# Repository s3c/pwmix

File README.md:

The pwmix project is a small hardware device that can alter PWM/PPM signals generated by common hobby remote controls. This allows enabling mixing for cheap RC transmitters, or where the receiver applies some mechanism that isn't desired. It is based on the Attiny85 but smaller micro controllers like the Attiny25 can  be used, you'll need a pretty steady hand to make it fit on the edge of the larger footprint though. 

The unit supports two inputs and two outputs, although these are identical and can potentially be used otherwise. With the micro controller facing upwards, the top left channel is input channel one, the bottom left channel is input two, the bottom right channel is output one, and the top right channel is output two. By convention, input one is considered the main input, and input two is considered the modulating input.

Since the Attiny85 has an inaccurate internal timer, rather than adding a crystal the unit does a clock sync to sync with the receiver. This is done by adjusting the internal clock using a binary search at startup, to match the expected pulse length with what is received. This is done on input channel one, and the expected value differs between code features.

The project was created with the following in mind:

* (DONE) Differential drive mixing - the main input takes a motor drive, while the second takes a servo turning signal. These are mixed together to output two motor drive signals mixed to provide differential drive. This allows the use of two motors to drive and steer, as opposed to a motor and a servo. Initial sync should be at mid stick (1.5mS PWM pulse)
* Servo limiting (planned) - the main input takes a servo input, while the optional second input takes a calibration servo signal. If the second signal is present, the minimum and maximum values are stored and saved in EEPROM. The output signals are mirrored and will never exeed the stored limits. To set the limits plug in both signals and vary the second signal between min/max. The input signal is scaled so full input deflection gives full limited output deflection. Initial sync should be at low stick (1mS PWM pulse)
* Fake Nitrous oxide (planned) - the main input takes a motor drive, while the second takes a enable signal. If the enable signal is greater than 3/4 full deflection, the mirrored outputs (following the motor drive signal) are allowed to swing to greater than 50%, if not, the output signals are limited to 50%. When this enable trigger is active, a timer decrements a 30 second limit, which limits the motor to 50% when depleted. This creates a fake boost mechanism, which gives a more dynamic nature to racing. Initial sync should be at mid stick (1.5mS PWM pulse)
* (DONE) PPM to PWM converter - Each board strips off the first two PPM channels and outputs them as PWM, then passes the remaining PPM signal along. This allows daisy chaining the PPM signal along the body of the plane so you only need to run one wire from the receiver and still be able to control all servos/motors, etc.

Known issues (Differential drive mixing):
* There seems to be a dead band/jitter of around 50uS for small values on input two in one direction, this also seems to reflect more on output one than output two for some reason. I don't really know why this is happening, I've confirmed that there is a tiny dead band/jitter on the input channel, but insignificant compared to the output. The inputs/outputs aren't handled differently in any way so some weird race condition is in play here. The most likely scenario is that the edge trigger interrupt fires just before the compare match timer, so the timer interrupt only fires after the edge has been processed, creating a dead band region. The ideal fix for this would be to use the compare match module to automatically turn off the output pins, but the hardware doesn't allow this, as the output pins aren't assigned to the compare match pins. I'll fix this if there's ever another revision. **Update: Ok, I managed to confirm that this was the problem, and I fixed the issue by making the pin change ISR non-blocking and adding a flag to avoid re-entry if another pin change occured. We still have some jitter but that's to be expected considering all the overhead and no crystal. The above fix would still be better though**

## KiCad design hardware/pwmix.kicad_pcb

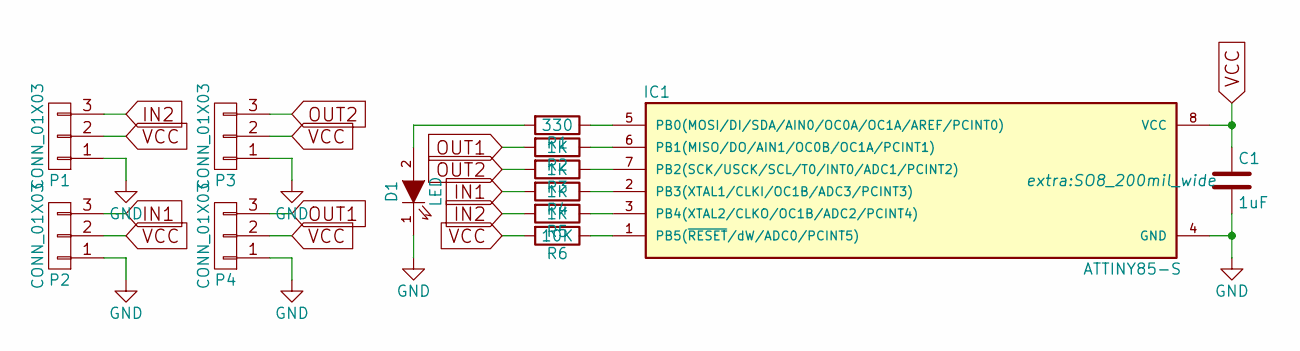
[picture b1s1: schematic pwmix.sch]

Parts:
C1: 1uF; C_0805
D1: LED; LED_0805
IC1: ATTINY85-S; SO8_200mil_wide
P1, P2, P3, P4: CONN_01X03; Pin_Header_Angled_1x03
R1: 330; R_0805
R2, R3, R4, R5: 1K; R_0805
R6: 10K; R_0805

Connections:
GND: C1.2, D1.1 (K), IC1.4 (GND), P1.1, P2.1, P3.1, P4.1
IN1: P2.3, R4.2
IN2: P1.3, R5.2
unnamed: D1.2 (A), R1.2
unnamed: IC1.1 (PB5(~RESET~/dW/ADC0/PCINT5)), R6.1
unnamed: IC1.2 (PB3(XTAL1/CLKI/OC1B/ADC3/PCINT3)), R4.1
unnamed: IC1.3 (PB4(XTAL2/CLKO/OC1B/ADC2/PCINT4)), R5.1
unnamed: IC1.5 (PB0(MOSI/DI/SDA/AIN0/OC0A/OC1A/AREF/PCI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), R1.1
unnamed: IC1.6 (PB1(MISO/DO/AIN1/OC0B/OC1A/PCINT1)), R2.1
unnamed: IC1.7 (PB2(SCK/USCK/SCL/T0/INT0/ADC1/PCINT2)), R3.1
OUT1: P4.3, R2.2
OUT2: P3.3, R3.2
VCC: C1.1, IC1.8 (VCC), P1.2, P2.2, P3.2, P4.2, R6.2

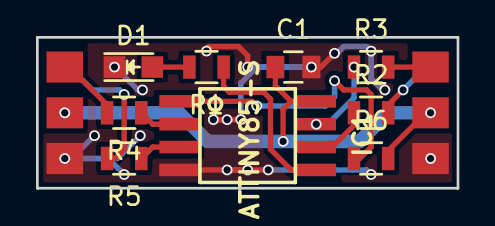
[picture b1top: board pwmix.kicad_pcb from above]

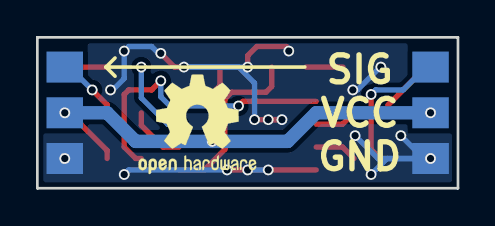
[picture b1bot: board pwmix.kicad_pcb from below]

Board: 2 copper layers, 23.4 x 8.4 mm, 13 parts (2 on the bottom side), 13 nets.

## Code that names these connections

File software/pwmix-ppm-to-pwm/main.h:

/*
 * main.h
 *
 * Created: 9/8/2016 4:50:35 AM
 *  Author: User
 */ 

#ifndef MAIN_H_
#define MAIN_H_

#define STATE_IDLE				0
#define STATE_WAIT				1
#define STATE_PULSE_1_START		2
#define STATE_PULSE_1_MID		3
#define STATE_PULSE_2_START		4
#define STATE_PULSE_2_MID		5

#define IN_CHANNEL_PPM			PB3

#define OUT_CHANNEL_ONE			PB1
#define OUT_CHANNEL_TWO			PB2
#define OUT_CHANNEL_LED			PB0
#define OUT_CHANNEL_PPM			PB4

#endif /* MAIN_H_ */

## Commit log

2016-08-24 Redid layout, as attiny85 footprint in kicad is way too small
2016-08-25 Regenerated and submitted gerbers
2016-09-11 First version fail, clock accuracy issues, going to redo with sync
2016-09-11 Redid with clock sync, seems to work but channel values differ, can't for the life of me figure out why
2016-09-11 Jitter is way better now, was a rounding error and unsigned to signed conversion, still some jitter on the one channel, which makes no sense since they should be equal
2016-09-15 Readme and comments updated
2016-09-17 Fixed the jitter/dead band issue
2017-04-01 Ehh, dunno, loads of stuff
2017-09-24 Added PPM to PWM converter
